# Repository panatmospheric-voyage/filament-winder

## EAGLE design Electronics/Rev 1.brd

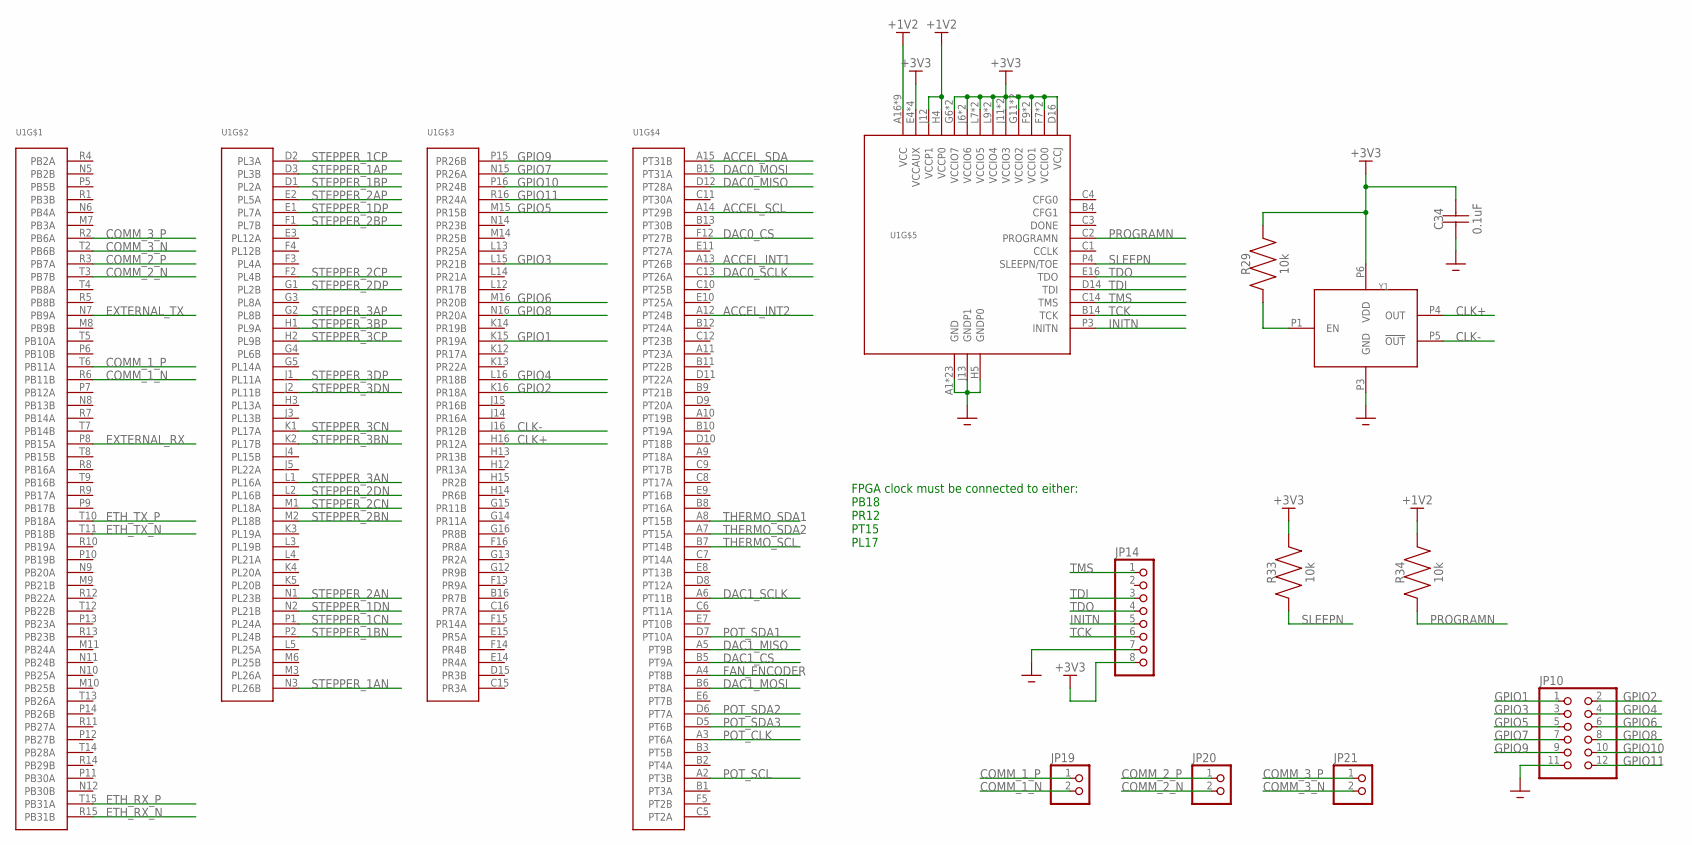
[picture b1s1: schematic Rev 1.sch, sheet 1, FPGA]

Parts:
C34: 0.1uF; 0805
JP10: PINHD-2X6; 2X06
JP14: PINHD-1X8; 1X08
JP19, JP20, JP21: PINHD-1X2; 1X02
R29, R33, R34: 10k; 0805
U1: LFXP6E-3FN256C; FBGA256
Y1: DSC1122B; ICDFN500X320X90-4

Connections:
+1V2: R34.P$2, U1.A16 (VCC), U1.D4 (VCC), U1.D13 (VCC), U1.E5 (VCC), U1.E12 (VCC), U1.H4 (VCCP0), U1.J12 (VCCP1), U1.M5 (VCC), U1.M12 (VCC), U1.N4 (VCC), U1.N13 (VCC); also elsewhere on the board
+3V3: C34.P$2, JP14.8, R29.P$2, R33.P$2, U1.D16 (VCCJ), U1.E4 (VCCAUX), U1.E13 (VCCAUX), U1.F7 (VCCIO0), U1.F8 (VCCIO0), U1.F9 (VCCIO1), U1.F10 (VCCIO1), U1.G6 (VCCIO7), U1.G11 (VCCIO2), U1.H6 (VCCIO7), U1.H11 (VCCIO2), U1.J6 (VCCIO6), U1.J11 (VCCIO3), U1.K6 (VCCIO6), U1.K11 (VCCIO3), U1.L7 (VCCIO5), U1.L8 (VCCIO5), U1.L9 (VCCIO4), U1.L10 (VCCIO4), U1.M4 (VCCAUX), U1.M13 (VCCAUX), Y1.P6 (VDD); also elsewhere on the board
ACCEL_INT1: U1.A13 (PT26B); also elsewhere on the board
ACCEL_INT2: U1.A12 (PT24B); also elsewhere on the board
ACCEL_SCL: U1.A14 (PT29B); also elsewhere on the board
ACCEL_SDA: U1.A15 (PT31B); also elsewhere on the board
CLK+: U1.H16 (PR12A), Y1.P4 (OUT)
CLK-: U1.J16 (PR12B), Y1.P5 (!OUT)
COMM_1_N: JP19.2, U1.R6 (PB11B)
COMM_1_P: JP19.1, U1.T6 (PB11A)
COMM_2_N: JP20.2, U1.T3 (PB7B)
COMM_2_P: JP20.1, U1.R3 (PB7A)
COMM_3_N: JP21.2, U1.T2 (PB6B)
COMM_3_P: JP21.1, U1.R2 (PB6A)
DAC0_CS: U1.F12 (PT27B); also elsewhere on the board
DAC0_MISO: U1.D12 (PT28A); also elsewhere on the board
DAC0_MOSI: U1.B15 (PT31A); also elsewhere on the board
DAC0_SCLK: U1.C13 (PT26A); also elsewhere on the board
DAC1_CS: U1.B5 (PT9A); also elsewhere on the board
DAC1_MISO: U1.A5 (PT9B); also elsewhere on the board
DAC1_MOSI: U1.B6 (PT8A); also elsewhere on the board
DAC1_SCLK: U1.A6 (PT11B); also elsewhere on the board
ETH_RX_N: U1.R15 (PB31B); also elsewhere on the board
ETH_RX_P: U1.T15 (PB31A); also elsewhere on the board
ETH_TX_N: U1.T11 (PB18B); also elsewhere on the board
ETH_TX_P: U1.T10 (PB18A); also elsewhere on the board
EXTERNAL_RX: U1.P8 (PB15A); also elsewhere on the board
EXTERNAL_TX: U1.N7 (PB9A); also elsewhere on the board
FAN_ENCODER: U1.A4 (PT8B); also elsewhere on the board
GND: C34.P$1, JP10.11, JP14.7, U1.A1 (GND), U1.F6 (GND), U1.F11 (GND), U1.G7 (GND), U1.G8 (GND), U1.G9 (GND), U1.G10 (GND), U1.H5 (GNDP0), U1.H7 (GND), U1.H8 (GND), U1.H9 (GND), U1.H10 (GND), U1.J7 (GND), U1.J8 (GND), U1.J9 (GND), U1.J10 (GND), U1.J13 (GNDP1), U1.K7 (GND), U1.K8 (GND), U1.K9 (GND), U1.K10 (GND), U1.L6 (GND), U1.L11 (GND), U1.T1 (GND), U1.T16 (GND), Y1.P3 (GND); also elsewhere on the board
GPIO1: JP10.1, U1.K15 (PR19A)
GPIO2: JP10.2, U1.K16 (PR18A)
GPIO3: JP10.3, U1.L15 (PR21B)
GPIO4: JP10.4, U1.L16 (PR18B)
GPIO5: JP10.5, U1.M15 (PR15B)
GPIO6: JP10.6, U1.M16 (PR20B)
GPIO7: JP10.7, U1.N15 (PR26A)
GPIO8: JP10.8, U1.N16 (PR20A)
GPIO9: JP10.9, U1.P15 (PR26B)
GPIO10: JP10.10, U1.P16 (PR24B)
GPIO11: JP10.12, U1.R16 (PR24A)
INITN: JP14.5, U1.P3 (INITN)
unnamed: R29.P$1, Y1.P1 (EN)
POT_CLK: U1.A3 (PT6A); also elsewhere on the board
POT_SCL: U1.A2 (PT3B); also elsewhere on the board
POT_SDA1: U1.D7 (PT10A); also elsewhere on the board
POT_SDA2: U1.D6 (PT7A); also elsewhere on the board
POT_SDA3: U1.D5 (PT6B); also elsewhere on the board
PROGRAMN: R34.P$1, U1.C2 (PROGRAMN)
SLEEPN: R33.P$1, U1.P4 (SLEEPN/TOE)
STEPPER_1AN: U1.N3 (PL26B); also elsewhere on the board
STEPPER_1AP: U1.D3 (PL3B); also elsewhere on the board
STEPPER_1BN: U1.P2 (PL24B); also elsewhere on the board
STEPPER_1BP: U1.D1 (PL2A); also elsewhere on the board
STEPPER_1CN: U1.P1 (PL24A); also elsewhere on the board
STEPPER_1CP: U1.D2 (PL3A); also elsewhere on the board
STEPPER_1DN: U1.N2 (PL21B); also elsewhere on the board
STEPPER_1DP: U1.E1 (PL7A); also elsewhere on the board
STEPPER_2AN: U1.N1 (PL23B); also elsewhere on the board
STEPPER_2AP: U1.E2 (PL5A); also elsewhere on the board
STEPPER_2BN: U1.M2 (PL18B); also elsewhere on the board
STEPPER_2BP: U1.F1 (PL7B); also elsewhere on the board
STEPPER_2CN: U1.M1 (PL18A); also elsewhere on the board
STEPPER_2CP: U1.F2 (PL4B); also elsewhere on the board
STEPPER_2DN: U1.L2 (PL16B); also elsewhere on the board
STEPPER_2DP: U1.G1 (PL2B); also elsewhere on the board
STEPPER_3AN: U1.L1 (PL16A); also elsewhere on the board
STEPPER_3AP: U1.G2 (PL8B); also elsewhere on the board
STEPPER_3BN: U1.K2 (PL17B); also elsewhere on the board
STEPPER_3BP: U1.H1 (PL9A); also elsewhere on the board
STEPPER_3CN: U1.K1 (PL17A); also elsewhere on the board
STEPPER_3CP: U1.H2 (PL9B); also elsewhere on the board
STEPPER_3DN: U1.J2 (PL11B); also elsewhere on the board
STEPPER_3DP: U1.J1 (PL11A); also elsewhere on the board
TCK: JP14.6, U1.B14 (TCK)
TDI: JP14.3, U1.D14 (TDI)
TDO: JP14.4, U1.E16 (TDO)
THERMO_SCL: U1.B7 (PT14B); also elsewhere on the board
THERMO_SDA1: U1.A8 (PT15B); also elsewhere on the board
THERMO_SDA2: U1.A7 (PT15A); also elsewhere on the board
TMS: JP14.1, U1.C14 (TMS)

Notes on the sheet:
FPGA clock must be connected to either: PB18 PR12 PT15 PL17

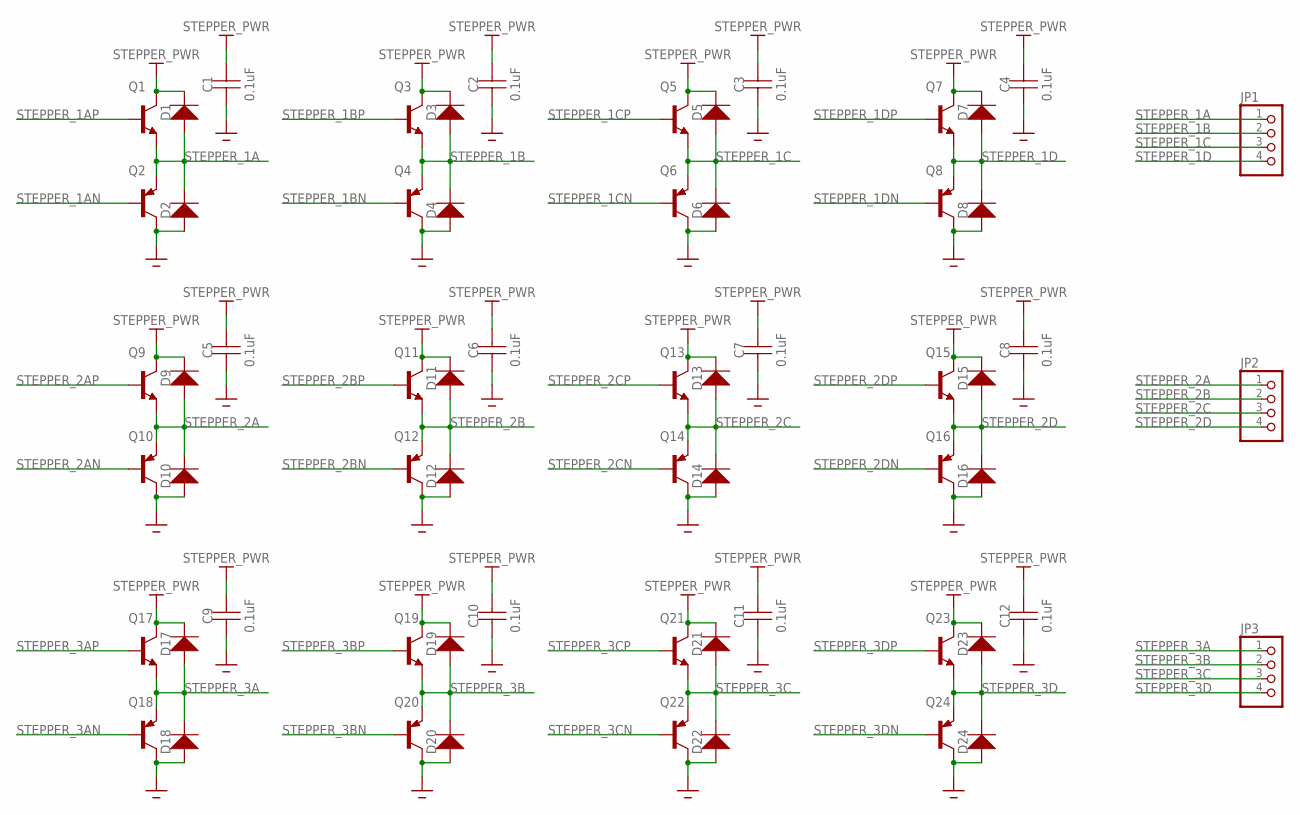
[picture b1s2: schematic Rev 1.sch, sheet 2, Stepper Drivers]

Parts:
C1, C2, C3, C4, C5, C6, C7, C8, C9, C10, C11, C12: 0.1uF; 0805
D1, D2, D3, D4, D5, D6, D7, D8, D9, D10, D11, D12, D13, D14, D15, D16, D17, D18, D19, D20, D21, D22, D23, D24: M7; DIOC5327X220
JP1, JP2, JP3: PINHD-1X4; 1X04
Q1, Q3, Q5, Q7, Q9, Q11, Q13, Q15, Q17, Q19, Q21, Q23: BCV27; SOT23-3
Q2, Q4, Q6, Q8, Q10, Q12, Q14, Q16, Q18, Q20, Q22, Q24: BCV26SOT23; SOT23-3

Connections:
GND: C1.P$1, C2.P$1, C3.P$1, C4.P$1, C5.P$1, C6.P$1, C7.P$1, C8.P$1, C9.P$1, C10.P$1, C11.P$1, C12.P$1, D2.1 (IN), D4.1 (IN), D6.1 (IN), D8.1 (IN), D10.1 (IN), D12.1 (IN), D14.1 (IN), D16.1 (IN), D18.1 (IN), D20.1 (IN), D22.1 (IN), D24.1 (IN), Q2.3 (C), Q4.3 (C), Q6.3 (C), Q8.3 (C), Q10.3 (C), Q12.3 (C), Q14.3 (C), Q16.3 (C), Q18.3 (C), Q20.3 (C), Q22.3 (C), Q24.3 (C); also elsewhere on the board
STEPPER_1A: D1.1 (IN), D2.2 (OUT), JP1.1, Q1.2 (E), Q2.2 (E)
STEPPER_1AN: Q2.1 (B); also elsewhere on the board
STEPPER_1AP: Q1.1 (B); also elsewhere on the board
STEPPER_1B: D3.1 (IN), D4.2 (OUT), JP1.2, Q3.2 (E), Q4.2 (E)
STEPPER_1BN: Q4.1 (B); also elsewhere on the board
STEPPER_1BP: Q3.1 (B); also elsewhere on the board
STEPPER_1C: D5.1 (IN), D6.2 (OUT), JP1.3, Q5.2 (E), Q6.2 (E)
STEPPER_1CN: Q6.1 (B); also elsewhere on the board
STEPPER_1CP: Q5.1 (B); also elsewhere on the board
STEPPER_1D: D7.1 (IN), D8.2 (OUT), JP1.4, Q7.2 (E), Q8.2 (E)
STEPPER_1DN: Q8.1 (B); also elsewhere on the board
STEPPER_1DP: Q7.1 (B); also elsewhere on the board
STEPPER_2A: D9.1 (IN), D10.2 (OUT), JP2.1, Q9.2 (E), Q10.2 (E)
STEPPER_2AN: Q10.1 (B); also elsewhere on the board
STEPPER_2AP: Q9.1 (B); also elsewhere on the board
STEPPER_2B: D11.1 (IN), D12.2 (OUT), JP2.2, Q11.2 (E), Q12.2 (E)
STEPPER_2BN: Q12.1 (B); also elsewhere on the board
STEPPER_2BP: Q11.1 (B); also elsewhere on the board
STEPPER_2C: D13.1 (IN), D14.2 (OUT), JP2.3, Q13.2 (E), Q14.2 (E)
STEPPER_2CN: Q14.1 (B); also elsewhere on the board
STEPPER_2CP: Q13.1 (B); also elsewhere on the board
STEPPER_2D: D15.1 (IN), D16.2 (OUT), JP2.4, Q15.2 (E), Q16.2 (E)
STEPPER_2DN: Q16.1 (B); also elsewhere on the board
STEPPER_2DP: Q15.1 (B); also elsewhere on the board
STEPPER_3A: D17.1 (IN), D18.2 (OUT), JP3.1, Q17.2 (E), Q18.2 (E)
STEPPER_3AN: Q18.1 (B); also elsewhere on the board
STEPPER_3AP: Q17.1 (B); also elsewhere on the board
STEPPER_3B: D19.1 (IN), D20.2 (OUT), JP3.2, Q19.2 (E), Q20.2 (E)
STEPPER_3BN: Q20.1 (B); also elsewhere on the board
STEPPER_3BP: Q19.1 (B); also elsewhere on the board
STEPPER_3C: D21.1 (IN), D22.2 (OUT), JP3.3, Q21.2 (E), Q22.2 (E)
STEPPER_3CN: Q22.1 (B); also elsewhere on the board
STEPPER_3CP: Q21.1 (B); also elsewhere on the board
STEPPER_3D: D23.1 (IN), D24.2 (OUT), JP3.4, Q23.2 (E), Q24.2 (E)
STEPPER_3DN: Q24.1 (B); also elsewhere on the board
STEPPER_3DP: Q23.1 (B); also elsewhere on the board
STEPPER_PWR: C1.P$2, C2.P$2, C3.P$2, C4.P$2, C5.P$2, C6.P$2, C7.P$2, C8.P$2, C9.P$2, C10.P$2, C11.P$2, C12.P$2, D1.2 (OUT), D3.2 (OUT), D5.2 (OUT), D7.2 (OUT), D9.2 (OUT), D11.2 (OUT), D13.2 (OUT), D15.2 (OUT), D17.2 (OUT), D19.2 (OUT), D21.2 (OUT), D23.2 (OUT), Q1.3 (C), Q3.3 (C), Q5.3 (C), Q7.3 (C), Q9.3 (C), Q11.3 (C), Q13.3 (C), Q15.3 (C), Q17.3 (C), Q19.3 (C), Q21.3 (C), Q23.3 (C); also elsewhere on the board

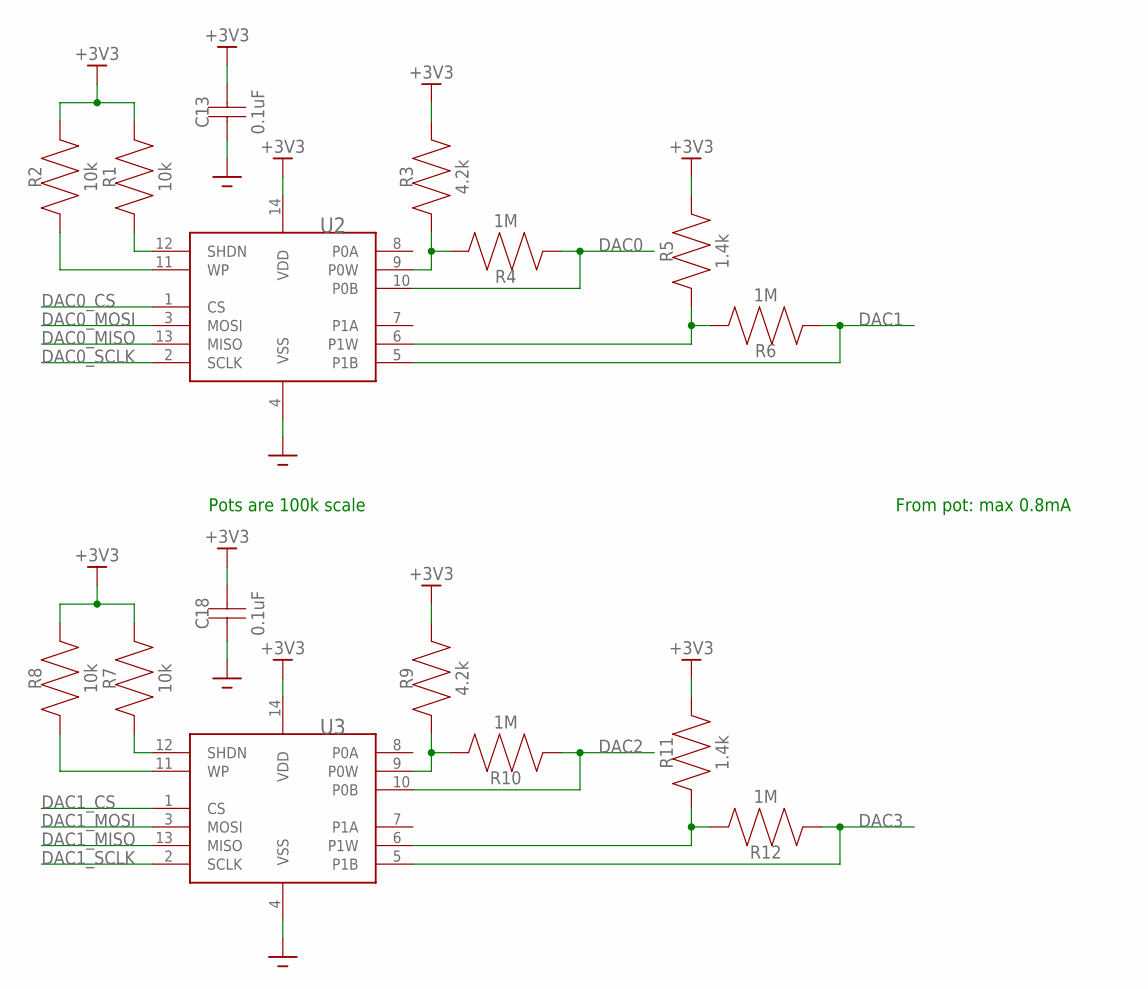
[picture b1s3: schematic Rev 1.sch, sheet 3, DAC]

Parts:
C13, C18: 0.1uF; 0805
R1, R2, R7, R8: 10k; 0805
R3, R9: 4.2k; 0805
R4, R6, R10, R12: 1M; 0805
R5, R11: 1.4k; 0805
U2, U3: MCP4251; SOP65P640X120-14

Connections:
+3V3: C13.P$2, C18.P$2, R1.P$2, R2.P$2, R3.P$2, R5.P$2, R7.P$2, R8.P$2, R9.P$2, R11.P$2, U2.14 (VDD), U3.14 (VDD); also elsewhere on the board
DAC0: R4.P$1, U2.10 (P0B); also elsewhere on the board
DAC0_CS: U2.1 (CS); also elsewhere on the board
DAC0_MISO: U2.13 (MISO); also elsewhere on the board
DAC0_MOSI: U2.3 (MOSI); also elsewhere on the board
DAC0_SCLK: U2.2 (SCLK); also elsewhere on the board
DAC1: R6.P$1, U2.5 (P1B); also elsewhere on the board
DAC1_CS: U3.1 (CS); also elsewhere on the board
DAC1_MISO: U3.13 (MISO); also elsewhere on the board
DAC1_MOSI: U3.3 (MOSI); also elsewhere on the board
DAC1_SCLK: U3.2 (SCLK); also elsewhere on the board
DAC2: R10.P$1, U3.10 (P0B); also elsewhere on the board
DAC3: R12.P$1, U3.5 (P1B); also elsewhere on the board
GND: C13.P$1, C18.P$1, U2.4 (VSS), U3.4 (VSS); also elsewhere on the board
unnamed: R1.P$1, U2.12 (SHDN)
unnamed: R2.P$1, U2.11 (WP)
unnamed: R3.P$1, R4.P$2, U2.9 (P0W)
unnamed: R5.P$1, R6.P$2, U2.6 (P1W)
unnamed: R7.P$1, U3.12 (SHDN)
unnamed: R8.P$1, U3.11 (WP)
unnamed: R9.P$1, R10.P$2, U3.9 (P0W)
unnamed: R11.P$1, R12.P$2, U3.6 (P1W)

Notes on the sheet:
From pot: max 0.8mA
Pots are 100k scale

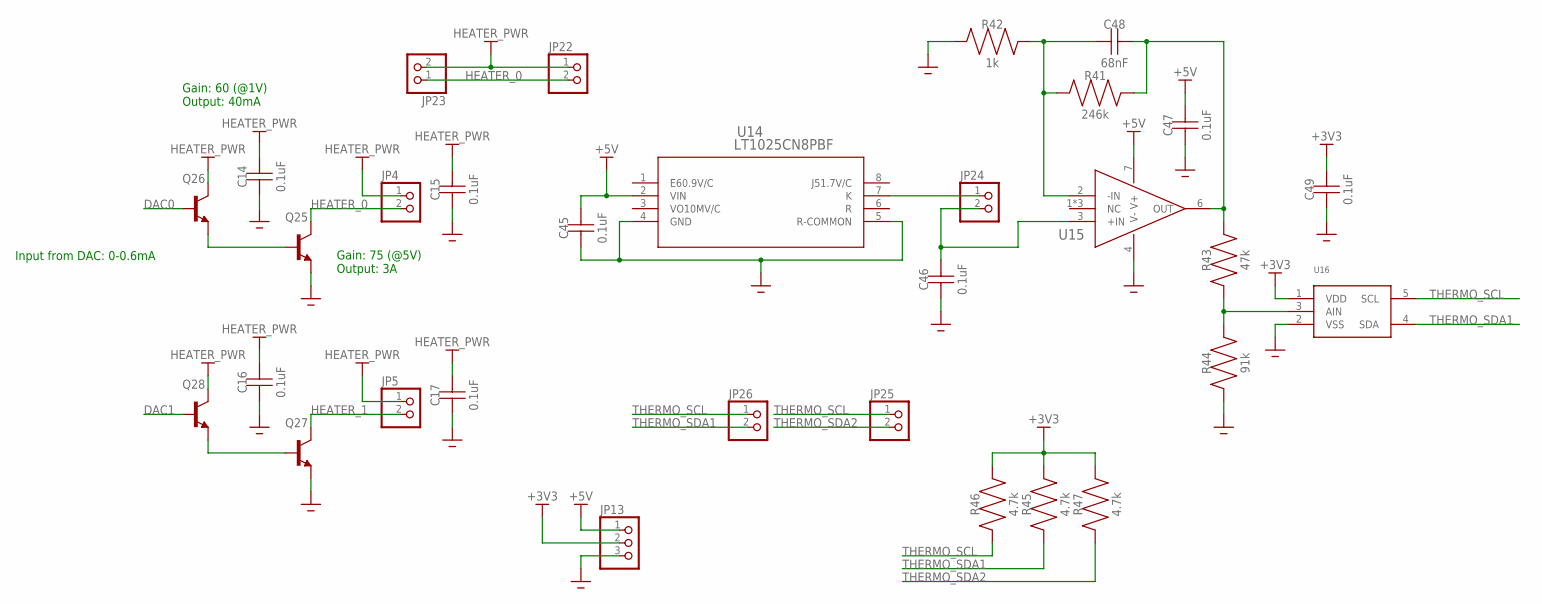
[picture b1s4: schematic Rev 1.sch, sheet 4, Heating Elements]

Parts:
C14, C15, C16, C17, C45, C46, C47, C49: 0.1uF; 0805
C48: 68nF; 0805
JP4, JP5, JP22, JP23, JP24, JP25, JP26: PINHD-1X2; 1X02
JP13: PINHD-1X3; 1X03
Q25, Q27: PBSS4360XFPBSS4360XF; SOT150P400X160-4
Q26, Q28: MMBT3904,215MMBT3904,215; SOT95P230X110-3
R41: 246k; 0805
R42: 1k; 0805
R43: 47k; 0805
R44: 91k; 0805
R45, R46, R47: 4.7k; 0805
U14: LT1025CN8PBF; N_8
U15: LTC1049CS8#PBF; SO-8_S
U16: MCP3021A1T-E/OTSOT23; SOT23-5

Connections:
+3V3: C49.P$2, JP13.2, R45.P$2, R46.P$2, R47.P$2, U16.1 (VDD); also elsewhere on the board
+5V: C45.P$2, C47.P$2, JP13.1, U14.2 (VIN), U15.7 (V+); also elsewhere on the board
DAC0: Q26.1 (B); also elsewhere on the board
DAC1: Q28.1 (B); also elsewhere on the board
GND: C14.P$1, C15.P$1, C16.P$1, C17.P$1, C45.P$1, C46.P$1, C47.P$1, C49.P$1, JP13.3, Q25.1 (E), Q27.1 (E), R42.P$1, R44.P$1, U14.4 (GND), U14.5 (R-COMMON), U15.4 (V-), U16.2 (VSS); also elsewhere on the board
HEATER_0: JP4.2, JP22.2, JP23.1, Q25.2 (C), Q25.4 (C)
HEATER_1: JP5.2, Q27.2 (C), Q27.4 (C)
HEATER_PWR: C14.P$2, C15.P$2, C16.P$2, C17.P$2, JP4.1, JP5.1, JP22.1, JP23.2, Q26.3 (C), Q28.3 (C); also elsewhere on the board
unnamed: Q25.3 (B), Q26.2 (E)
unnamed: Q27.3 (B), Q28.2 (E)
unnamed: C46.P$2, JP24.2, U15.3 (+IN)
unnamed: C48.P$1, R41.P$1, R42.P$2, U15.2 (-IN)
unnamed: JP24.1, U14.7 (K)
unnamed: C48.P$2, R41.P$2, R43.P$2, U15.6 (OUT)
unnamed: R43.P$1, R44.P$2, U16.3 (AIN)
THERMO_SCL: JP25.1, JP26.1, R46.P$1, U16.5 (SCL); also elsewhere on the board
THERMO_SDA1: JP26.2, R45.P$1, U16.4 (SDA); also elsewhere on the board
THERMO_SDA2: JP25.2, R47.P$1; also elsewhere on the board

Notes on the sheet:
Gain: 75 (@5V) Output: 3A
Gain: 60 (@1V) Output: 40mA
Input from DAC: 0-0.6mA

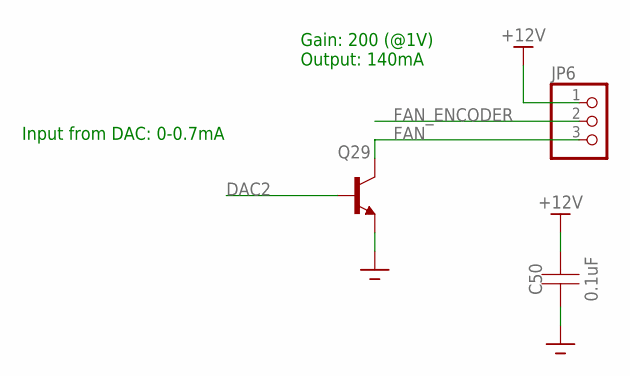
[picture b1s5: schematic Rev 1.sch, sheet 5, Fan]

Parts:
C50: 0.1uF; 0805
JP6: PINHD-1X3; 1X03
Q29: PBSS4360XFPBSS4360XF; SOT150P400X160-4

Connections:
+12V: C50.P$2, JP6.1; also elsewhere on the board
DAC2: Q29.3 (B); also elsewhere on the board
FAN: JP6.3, Q29.2 (C), Q29.4 (C)
FAN_ENCODER: JP6.2; also elsewhere on the board
GND: C50.P$1, Q29.1 (E); also elsewhere on the board

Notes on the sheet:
Gain: 200 (@1V) Output: 140mA
Input from DAC: 0-0.7mA

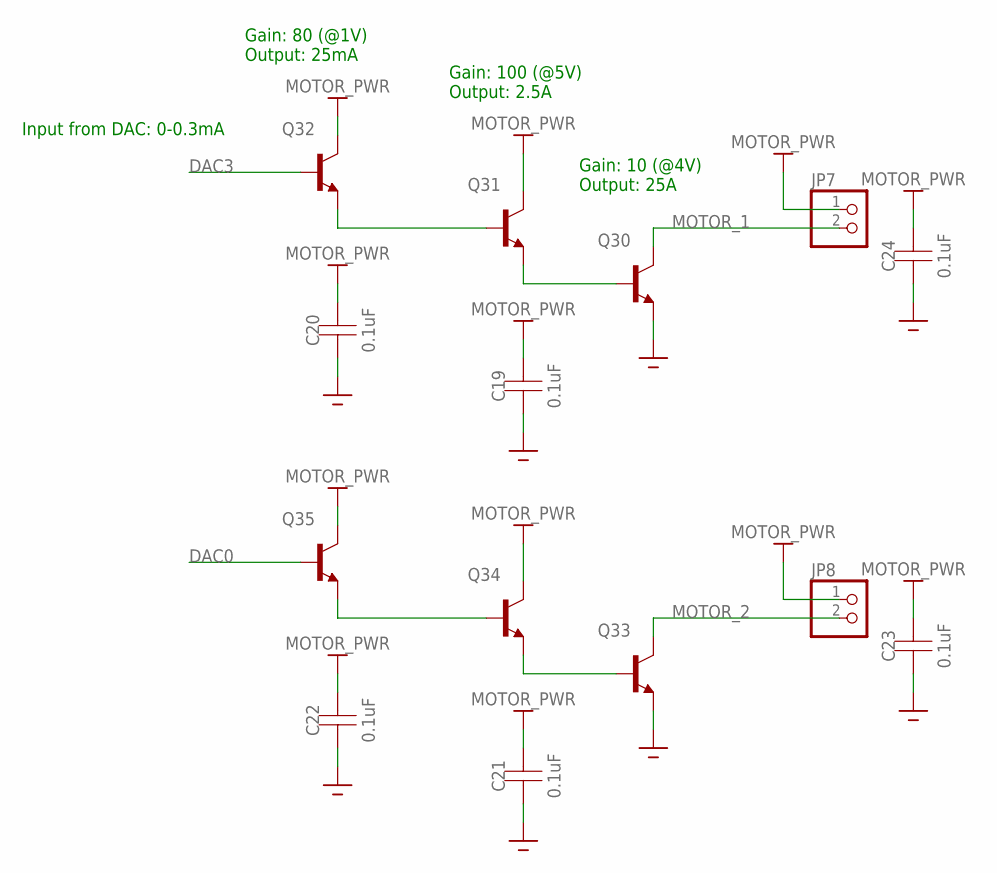
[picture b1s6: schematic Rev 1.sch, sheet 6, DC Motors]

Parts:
C19, C20, C21, C22, C23, C24: 0.1uF; 0805
JP7, JP8: PINHD-1X2; 1X02
Q30, Q33: TIP35CTIP35C; HDRV3W140P545_1X3_1560X508X838B
Q31, Q34: PBSS4360XFPBSS4360XF; SOT150P400X160-4
Q32, Q35: MMBT3904,215MMBT3904,215; SOT95P230X110-3

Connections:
DAC0: Q35.1 (B); also elsewhere on the board
DAC3: Q32.1 (B); also elsewhere on the board
GND: C19.P$1, C20.P$1, C21.P$1, C22.P$1, C23.P$1, C24.P$1, Q30.3 (E), Q33.3 (E); also elsewhere on the board
MOTOR_1: JP7.2, Q30.2 (C)
MOTOR_2: JP8.2, Q33.2 (C)
MOTOR_PWR: C19.P$2, C20.P$2, C21.P$2, C22.P$2, C23.P$2, C24.P$2, JP7.1, JP8.1, Q31.2 (C), Q31.4 (C), Q32.3 (C), Q34.2 (C), Q34.4 (C), Q35.3 (C); also elsewhere on the board
unnamed: Q33.1 (B), Q34.1 (E)
unnamed: Q30.1 (B), Q31.1 (E)
unnamed: Q31.3 (B), Q32.2 (E)
unnamed: Q34.3 (B), Q35.2 (E)

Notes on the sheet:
Gain: 10 (@4V) Output: 25A
Gain: 100 (@5V) Output: 2.5A
Gain: 80 (@1V) Output: 25mA
Input from DAC: 0-0.3mA

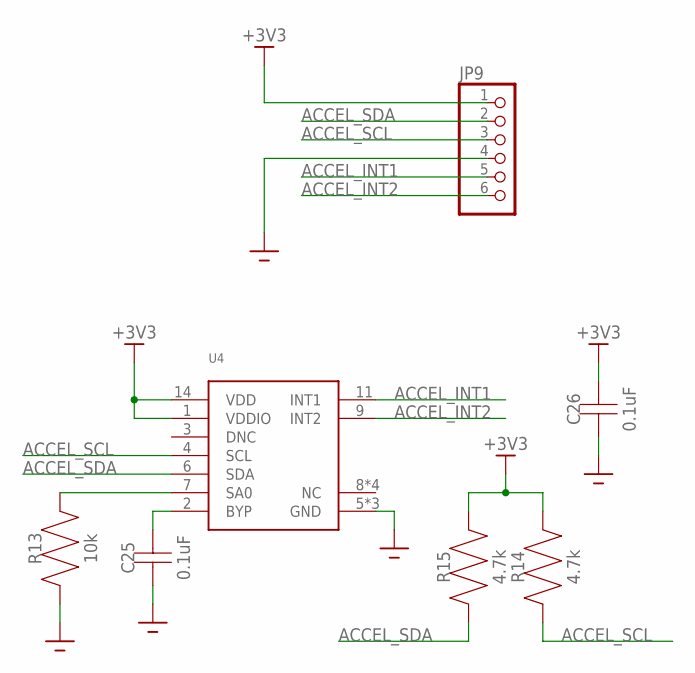
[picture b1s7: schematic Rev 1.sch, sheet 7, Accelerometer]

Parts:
C25, C26: 0.1uF; 0805
JP9: PINHD-1X6; 1X06
R13: 10k; 0805
R14, R15: 4.7k; 0805
U4: MMA8453QR116QFN; 16QFN

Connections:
+3V3: C26.P$2, JP9.1, R14.P$2, R15.P$2, U4.1 (VDDIO), U4.14 (VDD); also elsewhere on the board
ACCEL_INT1: JP9.5, U4.11 (INT1); also elsewhere on the board
ACCEL_INT2: JP9.6, U4.9 (INT2); also elsewhere on the board
ACCEL_SCL: JP9.3, R14.P$1, U4.4 (SCL); also elsewhere on the board
ACCEL_SDA: JP9.2, R15.P$1, U4.6 (SDA); also elsewhere on the board
GND: C25.P$1, C26.P$1, JP9.4, R13.P$1, U4.5 (GND), U4.10 (GND), U4.12 (GND); also elsewhere on the board
unnamed: C25.P$2, U4.2 (BYP)
unnamed: R13.P$2, U4.7 (SA0)

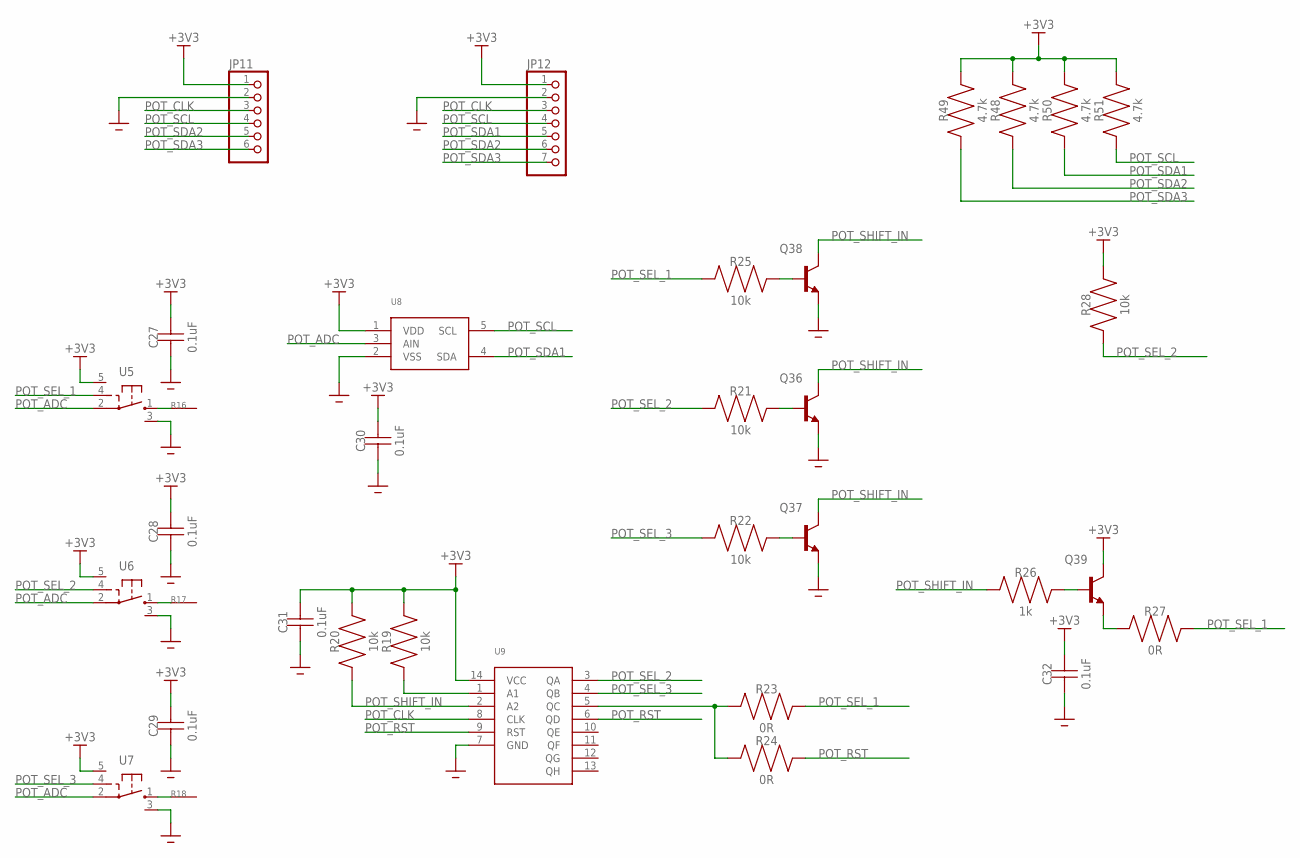
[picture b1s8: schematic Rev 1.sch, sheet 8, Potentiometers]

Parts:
C27, C28, C29, C30, C31, C32: 0.1uF; 0805
JP11: PINHD-1X6; 1X06
JP12: PINHD-1X7; 1X07
Q36, Q37, Q38, Q39: MMBT3904,215MMBT3904,215; SOT95P230X110-3
R16, R17, R18: POTENTIOMETER
R19, R20, R21, R22, R25, R28: 10k; 0805
R23, R24, R27: 0R; 0805
R26: 1k; 0805
R48, R49, R50, R51: 4.7k; 0805
U5, U6, U7: 74AHC1G66GW,125TSSOP6; TSSOP5
U8: MCP3021A1T-E/OTSOT23; SOT23-5
U9: MC74HC164BDR2GMC74HC164BDR2G; SOIC127P600X175-14

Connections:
+3V3: C27.P$2, C28.P$2, C29.P$2, C30.P$2, C31.P$2, C32.P$2, JP11.1, JP12.1, Q39.3 (C), R19.P$2, R20.P$2, R28.P$2, R48.P$2, R49.P$2, R50.P$2, R51.P$2, U5.5 (VCC), U6.5 (VCC), U7.5 (VCC), U8.1 (VDD), U9.14 (VCC); also elsewhere on the board
GND: C27.P$1, C28.P$1, C29.P$1, C30.P$1, C31.P$1, C32.P$1, JP11.2, JP12.2, Q36.2 (E), Q37.2 (E), Q38.2 (E), U5.3 (GND), U6.3 (GND), U7.3 (GND), U8.2 (VSS), U9.7 (GND); also elsewhere on the board
unnamed: R16.P$1, U5.1 (Y)
unnamed: R17.P$1, U6.1 (Y)
unnamed: R18.P$1, U7.1 (Y)
unnamed: Q36.1 (B), R21.P$2
unnamed: R19.P$1, U9.1 (A1)
unnamed: Q37.1 (B), R22.P$2
unnamed: R23.P$1, R24.P$1, U9.5 (QC)
unnamed: Q38.1 (B), R25.P$2
unnamed: Q39.1 (B), R26.P$2
unnamed: Q39.2 (E), R27.P$1
POT_ADC: U5.2 (Z), U6.2 (Z), U7.2 (Z), U8.3 (AIN)
POT_CLK: JP11.3, JP12.3, U9.8 (CLK); also elsewhere on the board
POT_RST: R24.P$2, U9.6 (QD), U9.9 (RST)
POT_SCL: JP11.4, JP12.4, R51.P$1, U8.5 (SCL); also elsewhere on the board
POT_SDA1: JP12.5, R50.P$1, U8.4 (SDA); also elsewhere on the board
POT_SDA2: JP11.5, JP12.6, R48.P$1; also elsewhere on the board
POT_SDA3: JP11.6, JP12.7, R49.P$1; also elsewhere on the board
POT_SEL_1: R23.P$2, R25.P$1, R27.P$2, U5.4 (E)
POT_SEL_2: R21.P$1, R28.P$1, U6.4 (E), U9.3 (QA)
POT_SEL_3: R22.P$1, U7.4 (E), U9.4 (QB)
POT_SHIFT_IN: Q36.3 (C), Q37.3 (C), Q38.3 (C), R20.P$1, R26.P$1, U9.2 (A2)

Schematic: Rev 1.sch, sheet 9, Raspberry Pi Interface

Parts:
C33: 1uF; 0805
U10: RPI

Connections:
+5V: C33.P$2, U10.2 (+5V), U10.4 (+5V); also elsewhere on the board
EXTERNAL_RX: U10.10 (RX); also elsewhere on the board
EXTERNAL_TX: U10.8 (TX); also elsewhere on the board
GND: C33.P$1, U10.6 (GND), U10.9 (GND), U10.14 (GND), U10.20 (GND), U10.25 (GND), U10.30 (GND), U10.34 (GND), U10.39 (GND); also elsewhere on the board

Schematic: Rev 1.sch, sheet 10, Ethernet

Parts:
C35, C36, C37, C38: 0.1uF; 0805
P1: 5-2301994-4
R30, R31, R32, R35: 49.9R; 0805

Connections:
+1V65: C37.P$2, C38.P$2, P1.P2 (TCTR), P1.P5 (RCTR); also elsewhere on the board
ETH_RX_N: P1.P6 (!RX), R35.P$2; also elsewhere on the board
ETH_RX_P: P1.P4 (RX), R32.P$2; also elsewhere on the board
ETH_TX_N: P1.P3 (!TX), R31.P$2; also elsewhere on the board
ETH_TX_P: P1.P1 (TX), R30.P$2; also elsewhere on the board
GND: C35.P$1, C36.P$1, C37.P$1, C38.P$1, P1.G1 (GND), P1.G2 (GND), P1.P8 (GND); also elsewhere on the board
unnamed: C35.P$2, R30.P$1, R31.P$1
unnamed: C36.P$2, R32.P$1, R35.P$1

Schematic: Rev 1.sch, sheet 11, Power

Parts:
C39, C40, C41, C42, C43, C44: 1uF; 0805
JP15, JP16, JP17: PINHD-1X1; 1X01
JP18: PINHD-1X3; 1X03
R36: 2.4k; 0805
R37: 7.5k; 0805
R38, R39, R40: 0R; 0805
U11, U12, U13: 3.3V; SOT230P700X180-4

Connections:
+1V2: C44.P$2, U13.2 (OUT), U13.4 (OUT); also elsewhere on the board
+1V65: C42.P$2, R36.P$2, U12.2 (OUT), U12.4 (OUT); also elsewhere on the board
+3V3: C40.P$2, C41.P$2, C43.P$2, U11.2 (OUT), U11.4 (OUT), U12.3 (IN), U13.3 (IN); also elsewhere on the board
+5V: C39.P$2, JP18.2, U11.3 (IN); also elsewhere on the board
+12V: JP18.1, R38.P$1, R39.P$1, R40.P$1; also elsewhere on the board
GND: C39.P$1, C40.P$1, C41.P$1, C42.P$1, C43.P$1, C44.P$1, JP18.3, R37.P$1, U11.1 (GND), U13.1 (GND); also elsewhere on the board
HEATER_PWR: JP16.1, R39.P$2; also elsewhere on the board
MOTOR_PWR: JP17.1, R40.P$2; also elsewhere on the board
unnamed: R36.P$1, R37.P$2, U12.1 (GND)
STEPPER_PWR: JP15.1, R38.P$2; also elsewhere on the board

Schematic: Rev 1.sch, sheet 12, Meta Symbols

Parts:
U$1: PCB_ACCEL
U$2: PCB_MAIN
U$3: PCB_POT
U$4: PCB_CARVER

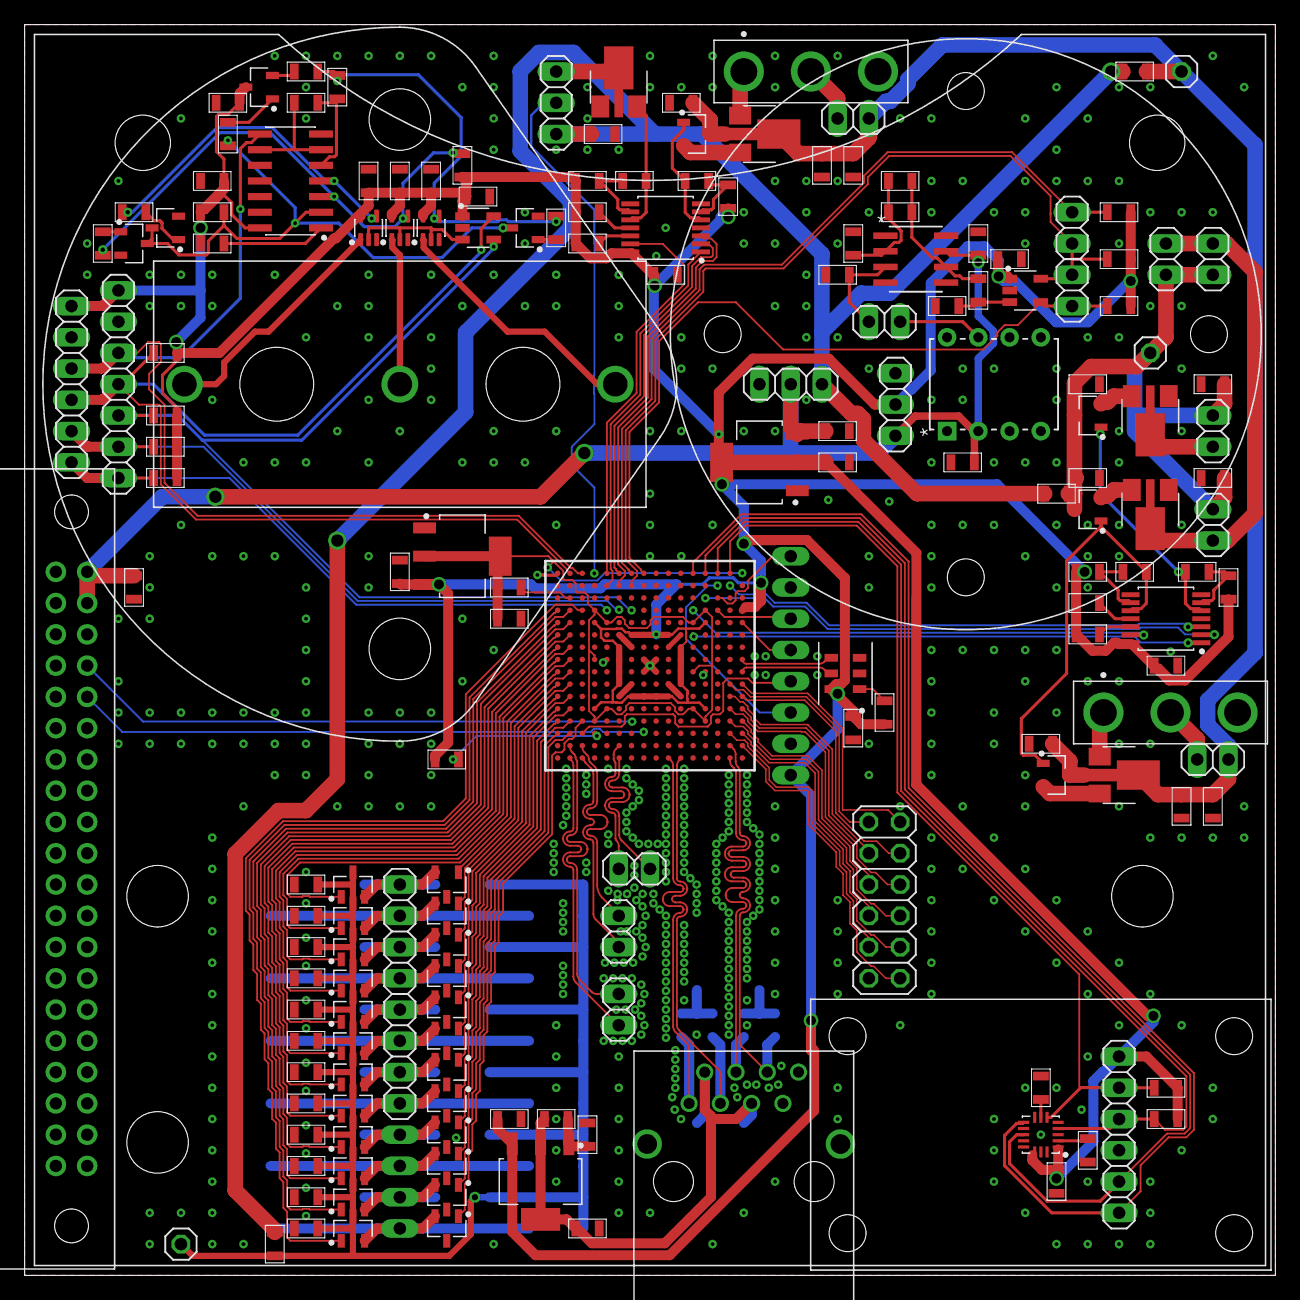
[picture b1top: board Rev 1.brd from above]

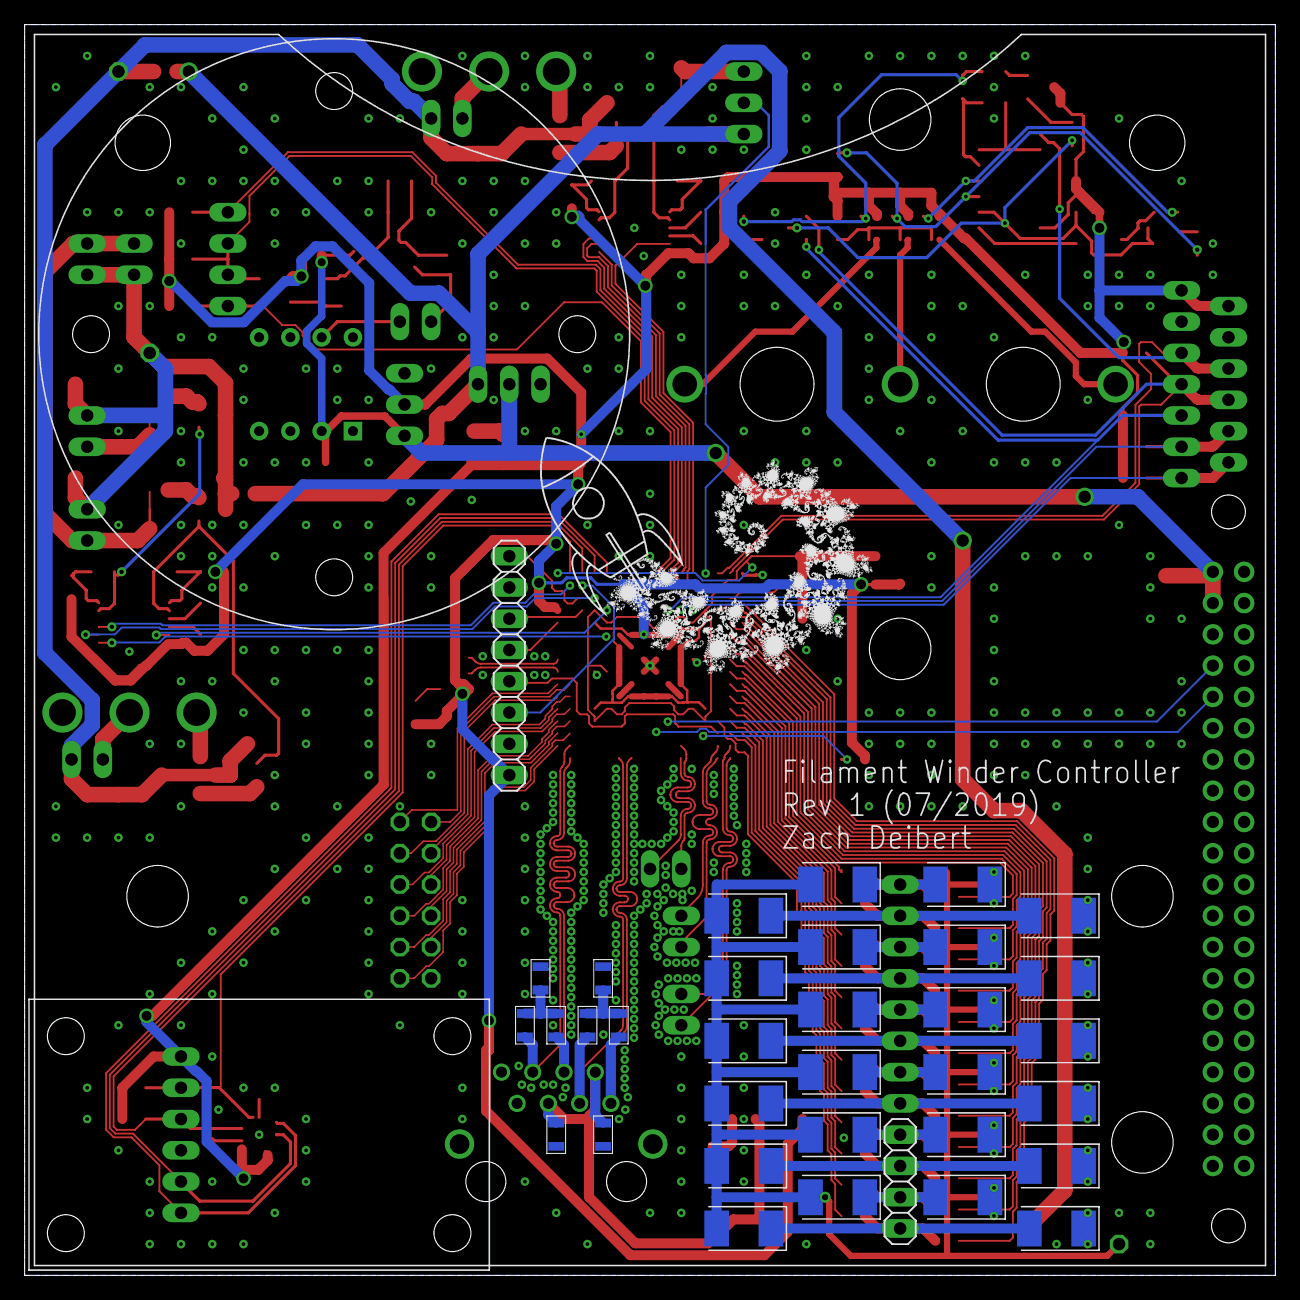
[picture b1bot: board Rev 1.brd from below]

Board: 2 copper layers, 101.6 x 101.6 mm, 212 parts (34 on the bottom side), 148 nets.

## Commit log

2019-07-26 Created Eagle project
2019-07-26 Created initial version of parts
2019-07-26 2/12 symbols and footprints created
2019-07-27 Hating Zach.
    Zach shouldn't be allowed to us FPGA's with 256 pins.
2019-07-27 Did a bunch of schematic work
2019-07-27 Did most of the rest of the schematic
2019-07-27 Finished more of the schematic
2019-07-27 Added power circuitry
2019-07-28 Cleaned up schematic some
2019-07-28 Started board layout
2019-07-28 Layed out board
2019-07-28 Added GPIO pins
2019-07-28 Updated silk screen
2020-02-10 Redesigned pulley injection mold
